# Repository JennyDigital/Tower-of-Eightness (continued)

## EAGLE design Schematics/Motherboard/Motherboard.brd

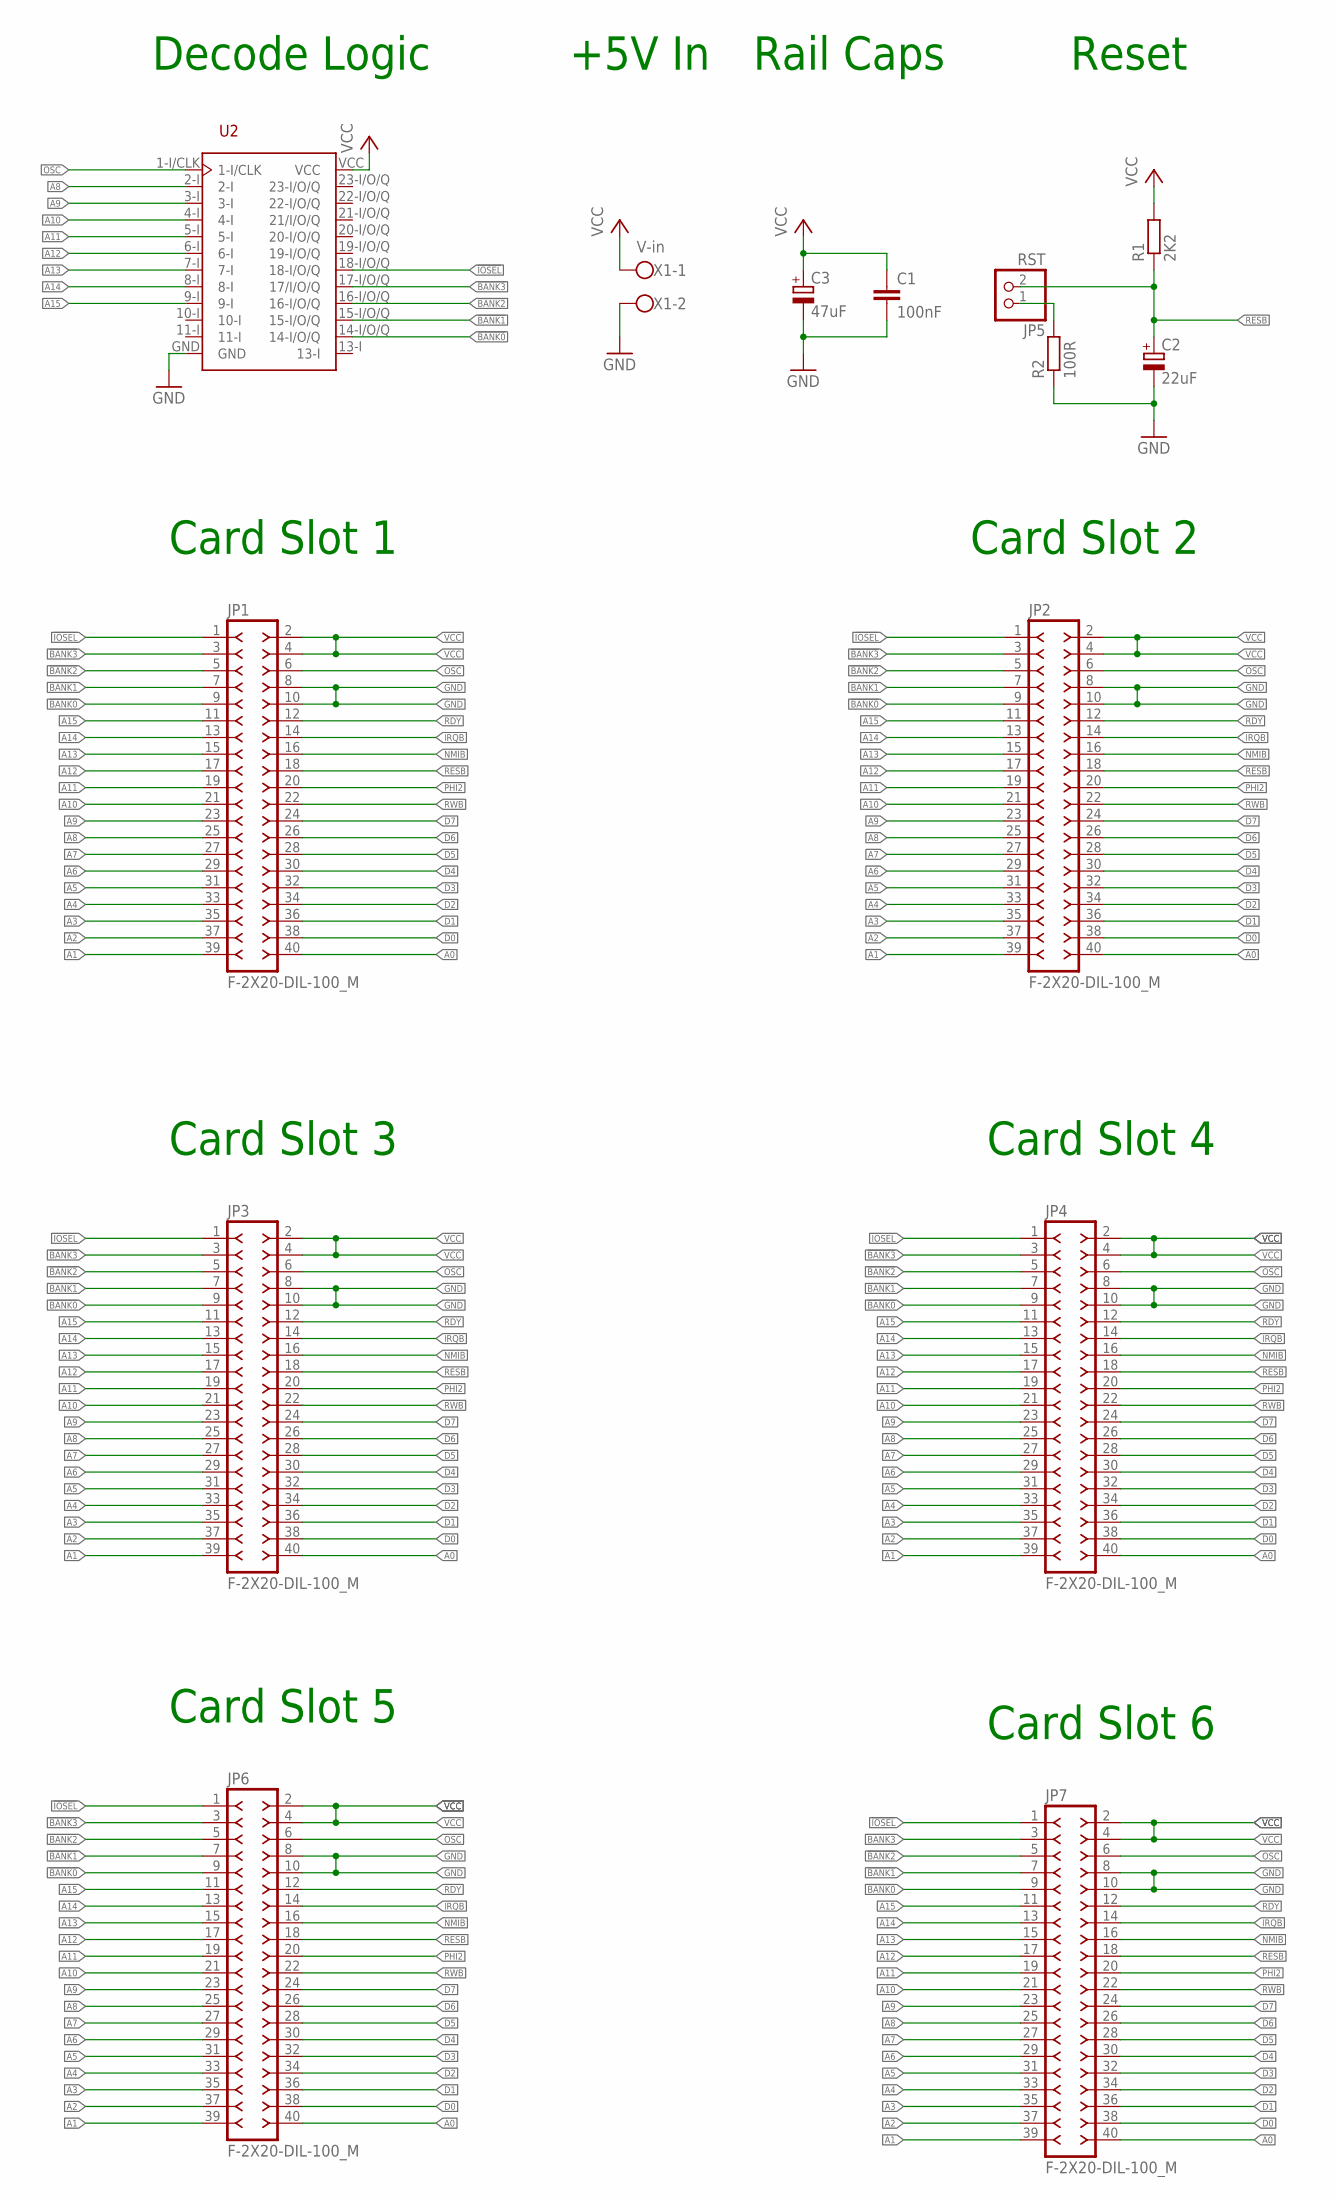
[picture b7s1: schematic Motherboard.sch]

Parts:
C1: 100nF; C050-025X075
C2: 22uF; E2-5
C3: 47uF; E2,5-7
JP1, JP2, JP3, JP4, JP6, JP7: F-2X20-DIL-100_M; DIL-100-2X20_M
JP5: RST; 1X02
R1: 2K2; 0207/10
R2: 100R; 0207/10
U2: GAL22V10D-DIP; DIP24
X1: V-in; W237-102

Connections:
!BANK0: JP1.9, JP2.9, JP3.9, JP4.9, JP6.9, JP7.9, U2.14-I/O/Q
!BANK1: JP1.7, JP2.7, JP3.7, JP4.7, JP6.7, JP7.7, U2.15-I/O/Q
!BANK2: JP1.5, JP2.5, JP3.5, JP4.5, JP6.5, JP7.5, U2.16-I/O/Q
!BANK3: JP1.3, JP2.3, JP3.3, JP4.3, JP6.3, JP7.3, U2.17-I/O/Q (17/I/O/Q)
!IOSEL: JP1.1, JP2.1, JP3.1, JP4.1, JP6.1, JP7.1, U2.18-I/O/Q
A0: JP1.40, JP2.40, JP3.40, JP4.40, JP6.40, JP7.40
A1: JP1.39, JP2.39, JP3.39, JP4.39, JP6.39, JP7.39
A2: JP1.37, JP2.37, JP3.37, JP4.37, JP6.37, JP7.37
A3: JP1.35, JP2.35, JP3.35, JP4.35, JP6.35, JP7.35
A4: JP1.33, JP2.33, JP3.33, JP4.33, JP6.33, JP7.33
A5: JP1.31, JP2.31, JP3.31, JP4.31, JP6.31, JP7.31
A6: JP1.29, JP2.29, JP3.29, JP4.29, JP6.29, JP7.29
A7: JP1.27, JP2.27, JP3.27, JP4.27, JP6.27, JP7.27
A8: JP1.25, JP2.25, JP3.25, JP4.25, JP6.25, JP7.25, U2.2-I
A9: JP1.23, JP2.23, JP3.23, JP4.23, JP6.23, JP7.23, U2.3-I
A10: JP1.21, JP2.21, JP3.21, JP4.21, JP6.21, JP7.21, U2.4-I
A11: JP1.19, JP2.19, JP3.19, JP4.19, JP6.19, JP7.19, U2.5-I
A12: JP1.17, JP2.17, JP3.17, JP4.17, JP6.17, JP7.17, U2.6-I
A13: JP1.15, JP2.15, JP3.15, JP4.15, JP6.15, JP7.15, U2.7-I
A14: JP1.13, JP2.13, JP3.13, JP4.13, JP6.13, JP7.13, U2.8-I
A15: JP1.11, JP2.11, JP3.11, JP4.11, JP6.11, JP7.11, U2.9-I
D0: JP1.38, JP2.38, JP3.38, JP4.38, JP6.38, JP7.38
D1: JP1.36, JP2.36, JP3.36, JP4.36, JP6.36, JP7.36
D2: JP1.34, JP2.34, JP3.34, JP4.34, JP6.34, JP7.34
D3: JP1.32, JP2.32, JP3.32, JP4.32, JP6.32, JP7.32
D4: JP1.30, JP2.30, JP3.30, JP4.30, JP6.30, JP7.30
D5: JP1.28, JP2.28, JP3.28, JP4.28, JP6.28, JP7.28
D6: JP1.26, JP2.26, JP3.26, JP4.26, JP6.26, JP7.26
D7: JP1.24, JP2.24, JP3.24, JP4.24, JP6.24, JP7.24
GND: C1.2, C2.-, C3.-, JP1.8, JP1.10, JP2.8, JP2.10, JP3.8, JP3.10, JP4.8, JP4.10, JP6.8, JP6.10, JP7.8, JP7.10, R2.1, U2.GND, X1.2
IRQB: JP1.14, JP2.14, JP3.14, JP4.14, JP6.14, JP7.14
unnamed: JP5.1, R2.2
NMIB: JP1.16, JP2.16, JP3.16, JP4.16, JP6.16, JP7.16
OSC: JP1.6, JP2.6, JP3.6, JP4.6, JP6.6, JP7.6, U2.1-I/CLK
PHI2: JP1.20, JP2.20, JP3.20, JP4.20, JP6.20, JP7.20
RDY: JP1.12, JP2.12, JP3.12, JP4.12, JP6.12, JP7.12
RESB: C2.+, JP1.18, JP2.18, JP3.18, JP4.18, JP5.2, JP6.18, JP7.18, R1.1
RWB: JP1.22, JP2.22, JP3.22, JP4.22, JP6.22, JP7.22
VCC: C1.1, C3.+, JP1.2, JP1.4, JP2.2, JP2.4, JP3.2, JP3.4, JP4.2, JP4.4, JP6.2, JP6.4, JP7.2, JP7.4, R1.2, U2.VCC, X1.1

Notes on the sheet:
Decode Logic
Card Slot 1
Card Slot 2
Card Slot 3
Card Slot 4
Reset
+5V In
Rail Caps
Card Slot 5
Card Slot 6

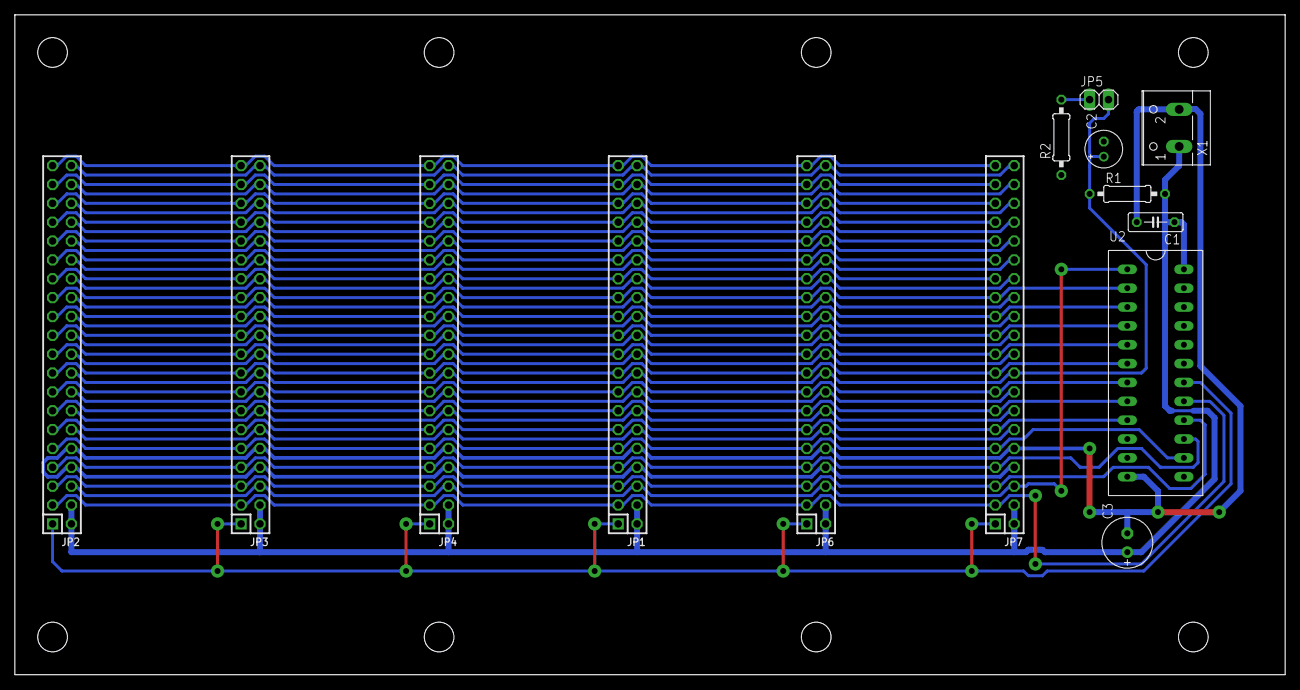
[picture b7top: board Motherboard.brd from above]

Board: 2 copper layers, 171.1 x 88.9 mm, 14 parts (0 on the bottom side), 39 nets.

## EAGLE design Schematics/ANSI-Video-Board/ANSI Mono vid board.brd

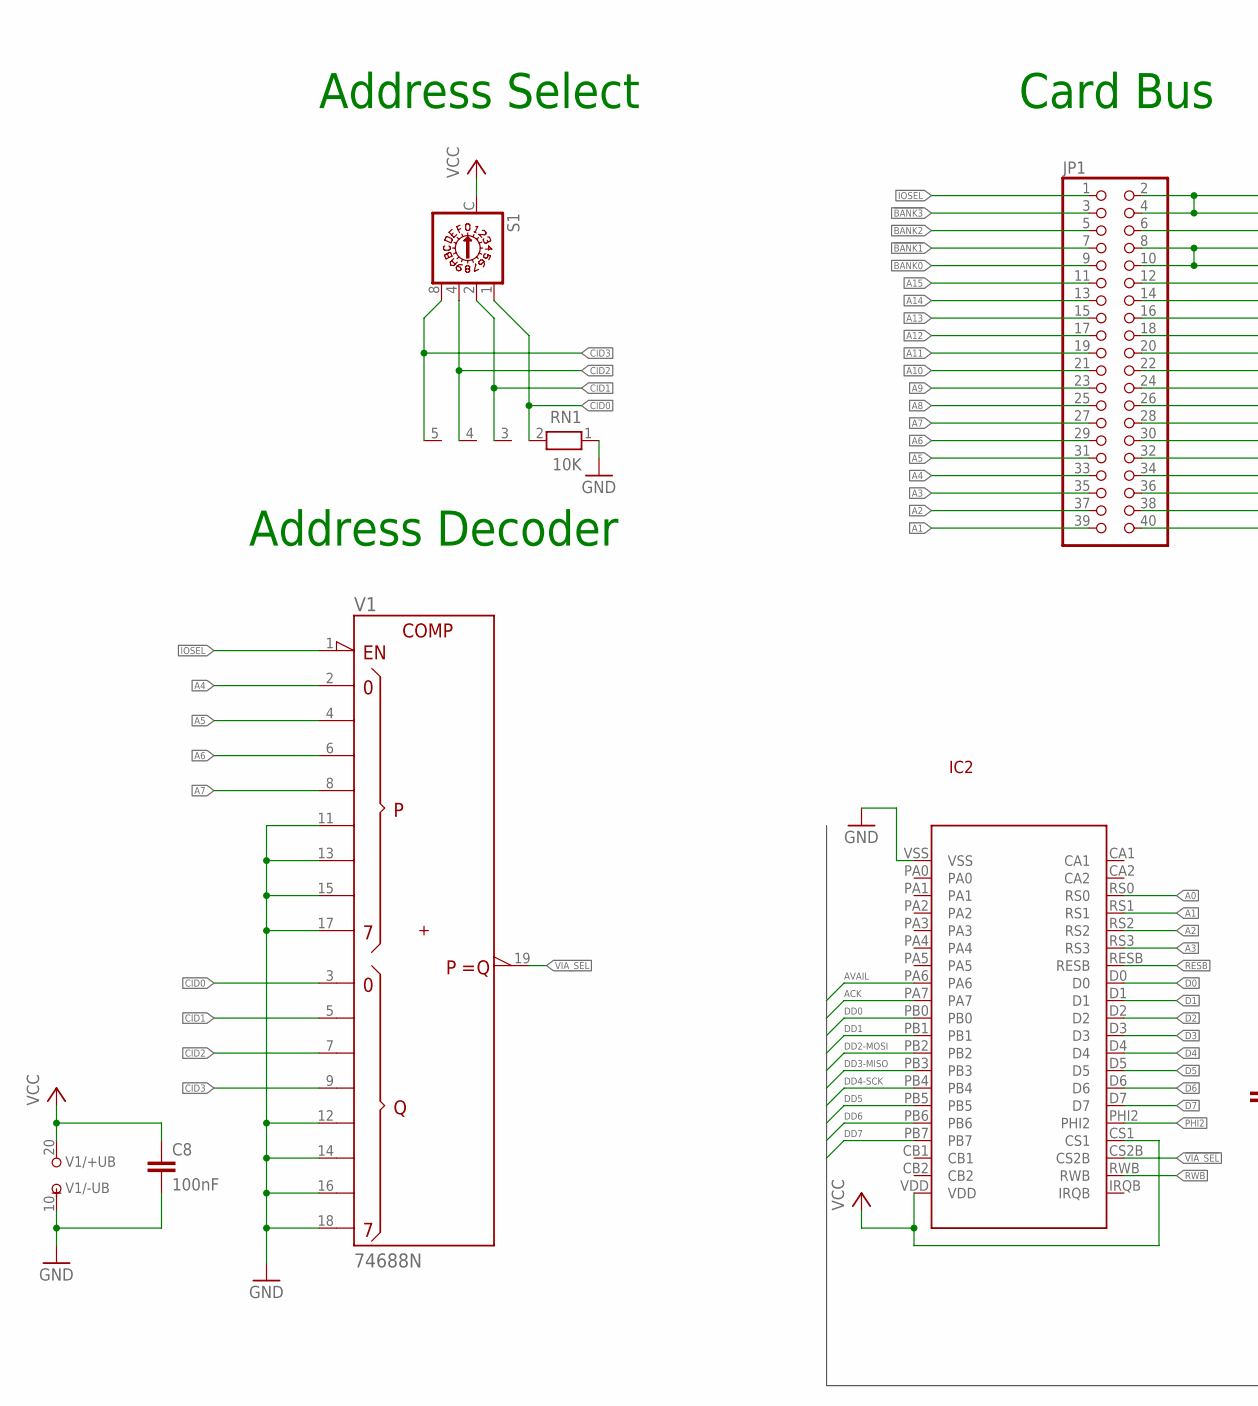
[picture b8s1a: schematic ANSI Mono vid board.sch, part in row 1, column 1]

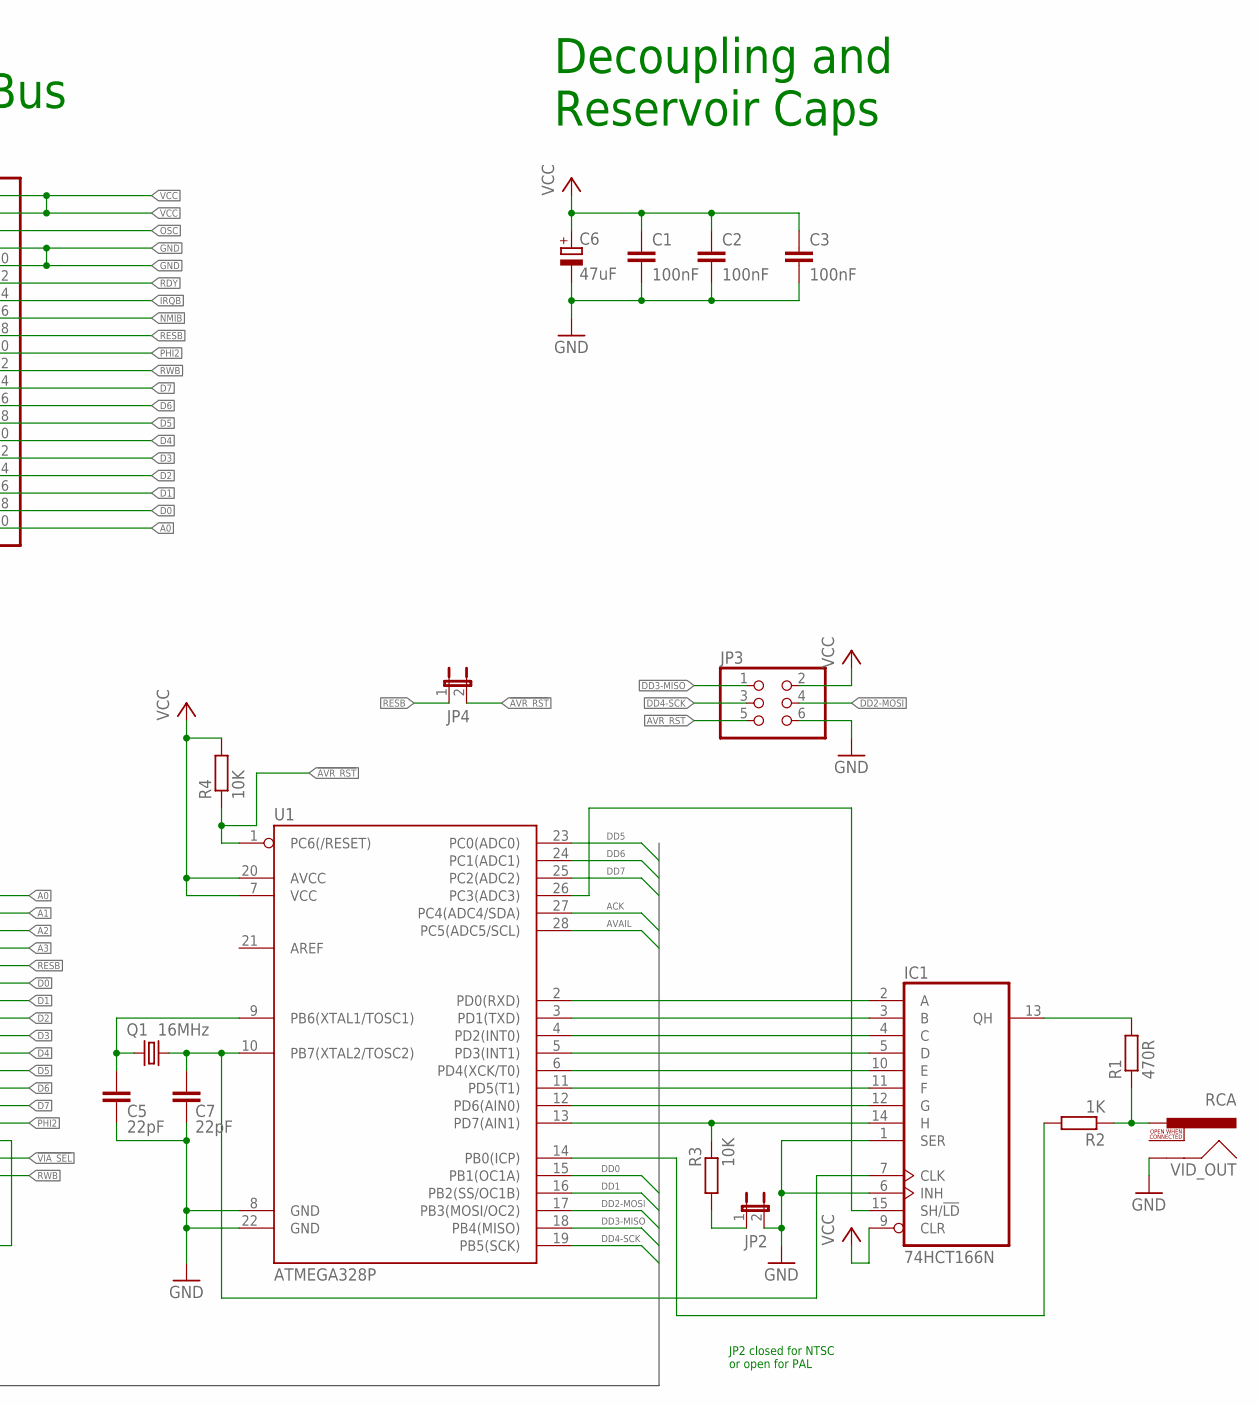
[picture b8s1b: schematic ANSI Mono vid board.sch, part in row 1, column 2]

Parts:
C1, C2, C8: 100nF; C050-025X075
C3: 100nF; C025-025X050
C5, C7: 22pF; C050-025X075
C6: 47uF; E2,5-7
IC1: 74HCT166N; DIL16
IC2: W65C22; W65C22-DIP
JP1: PINHD-2X20/90; 2X20/90
JP2, JP4: JP1E; JP1
JP3: PINHD-2X3; 2X03
Q1: 16MHz; HC49U-V
R1: 470R; 0207/10
R2: 1K; 0207/10
R3: 10K; 0207/2V
R4: 10K; 0207/7
RN1: 10K; RN-5
S1: DRR3016; DRR3010
U1: ATMEGA328P; DIL28-3
V1: 74688N; DIL20
VID_OUT: RCA

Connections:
!AVR_RST: JP3.5, JP4.2, R4.1, U1.1 (PC6(/RESET))
!BANK0: JP1.9
!BANK1: JP1.7
!BANK2: JP1.5
!BANK3: JP1.3
!IOSEL: JP1.1, V1.1 (!G)
!VIA_SEL: IC2.CS2B, V1.19 (!P=Q)
A0: IC2.RS0, JP1.40
A1: IC2.RS1, JP1.39
A2: IC2.RS2, JP1.37
A3: IC2.RS3, JP1.35
A4: JP1.33, V1.2 (P0)
A5: JP1.31, V1.4 (P1)
A6: JP1.29, V1.6 (P2)
A7: JP1.27, V1.8 (P3)
A8: JP1.25
A9: JP1.23
A10: JP1.21
A11: JP1.19
A12: JP1.17
A13: JP1.15
A14: JP1.13
A15: JP1.11
ACK: IC2.PA7, U1.27 (PC4(ADC4/SDA))
AVAIL: IC2.PA6, U1.28 (PC5(ADC5/SCL))
CID0: RN1.2, S1.1, V1.3 (Q0)
CID1: RN1.3, S1.2, V1.5 (Q1)
CID2: RN1.4, S1.4, V1.7 (Q2)
CID3: RN1.5, S1.8, V1.9 (Q3)
D0: IC2.D0, JP1.38
D1: IC2.D1, JP1.36
D2: IC2.D2, JP1.34
D3: IC2.D3, JP1.32
D4: IC2.D4, JP1.30
D5: IC2.D5, JP1.28
D6: IC2.D6, JP1.26
D7: IC2.D7, JP1.24
DD0: IC2.PB0, U1.15 (PB1(OC1A))
DD1: IC2.PB1, U1.16 (PB2(SS/OC1B))
DD2-MOSI: IC2.PB2, JP3.4, U1.17 (PB3(MOSI/OC2))
DD3-MISO: IC2.PB3, JP3.1, U1.18 (PB4(MISO))
DD4-SCK: IC2.PB4, JP3.3, U1.19 (PB5(SCK))
DD5: IC2.PB5, U1.23 (PC0(ADC0))
DD6: IC2.PB6, U1.24 (PC1(ADC1))
DD7: IC2.PB7, U1.25 (PC2(ADC2))
GND: C1.2, C2.2, C3.2, C5.2, C6.-, C7.2, C8.2, IC1.1 (SER), IC1.6 (INH), IC1.8 (GND), IC2.VSS, JP1.8, JP1.10, JP2.2, JP3.6, RN1.1, U1.8 (GND), U1.22 (GND), V1.10 (-UB), V1.11 (P4), V1.12 (Q4), V1.13 (P5), V1.14 (Q5), V1.15 (P6), V1.16 (Q6), V1.17 (P7), V1.18 (Q7), VID_OUT.SHELL
IRQB: JP1.14
unnamed: JP2.1, R3.1
unnamed: C5.1, Q1.2, U1.9 (PB6(XTAL1/TOSC1))
unnamed: C7.1, IC1.7 (CLK), Q1.1, U1.10 (PB7(XTAL2/TOSC2))
unnamed: IC1.2 (A), U1.2 (PD0(RXD))
unnamed: IC1.3 (B), U1.3 (PD1(TXD))
unnamed: IC1.4 (C), U1.4 (PD2(INT0))
unnamed: IC1.5 (D), U1.5 (PD3(INT1))
unnamed: IC1.10 (E), U1.6 (PD4(XCK/T0))
unnamed: IC1.11 (F), U1.11 (PD5(T1))
unnamed: IC1.12 (G), U1.12 (PD6(AIN0))
unnamed: IC1.14 (H), R3.2, U1.13 (PD7(AIN1))
unnamed: IC1.13 (QH), R1.2
unnamed: R2.2, U1.14 (PB0(ICP))
unnamed: IC1.15 (SH/!LD), U1.26 (PC3(ADC3))
unnamed: R1.1, R2.1, VID_OUT.PIN
NMIB: JP1.16
OSC: JP1.6
PHI2: IC2.PHI2, JP1.20
RDY: JP1.12
RESB: IC2.RESB, JP1.18, JP4.1
RWB: IC2.RWB, JP1.22
VCC: C1.1, C2.1, C3.1, C6.+, C8.1, IC1.9 (CLR), IC1.16 (VCC), IC2.CS1, IC2.VDD, JP1.2, JP1.4, JP3.2, R4.2, S1.C, U1.7 (VCC), U1.20 (AVCC), V1.20 (+UB)

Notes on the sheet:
Card Bus
Decoupling and Reservoir Caps
JP2 closed for NTSC or open for PAL
Address Select
Address Decoder

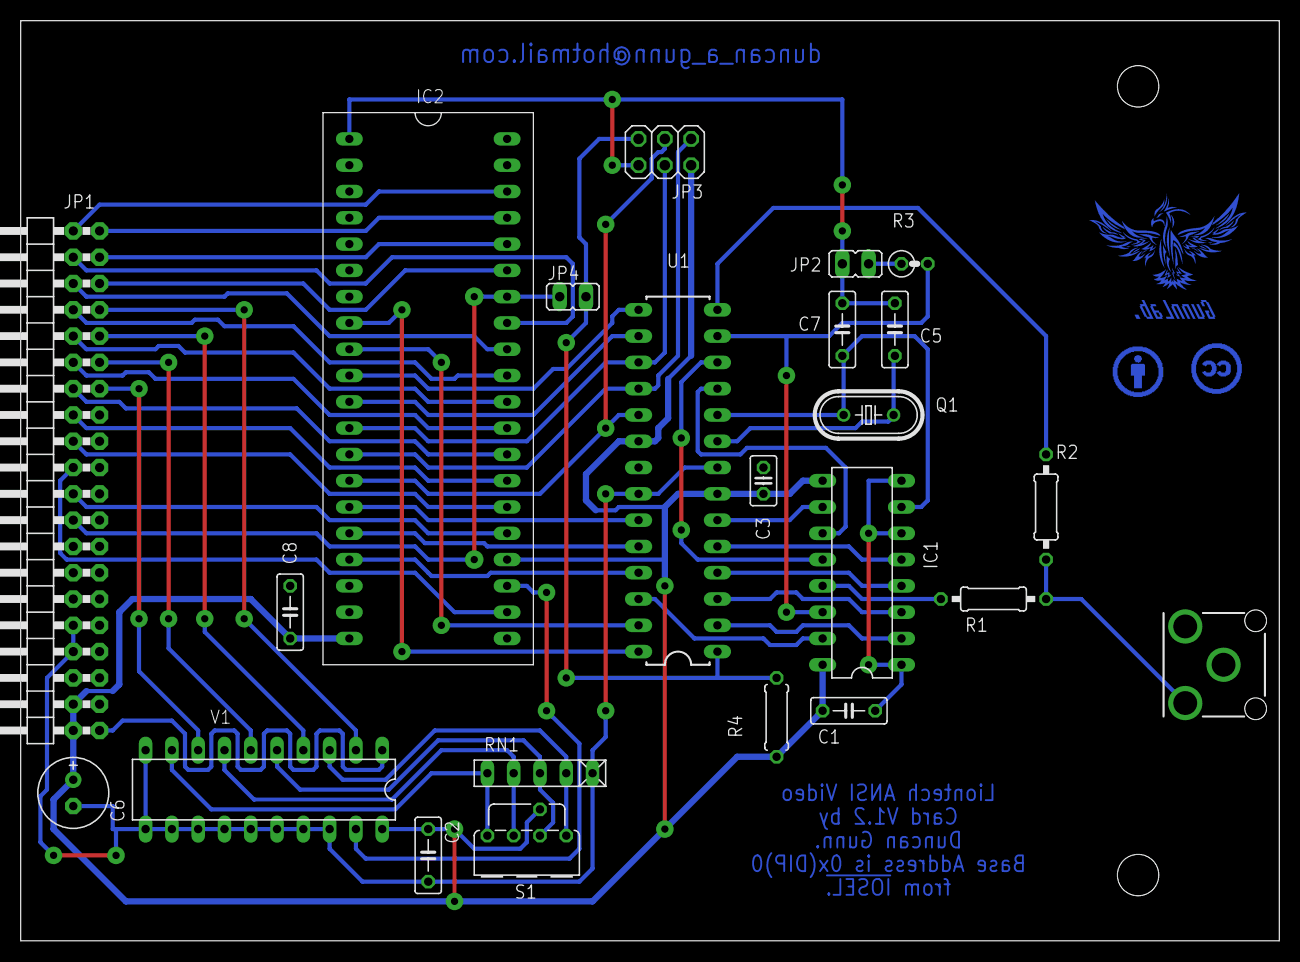
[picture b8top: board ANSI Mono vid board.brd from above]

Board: 2 copper layers, 121.6 x 88.9 mm, 26 parts (0 on the bottom side), 53 nets.

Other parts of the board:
U$1: LIONTECH
U$2: CC
U$3: BY

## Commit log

2018-06-14 First upload of project
2018-06-14 Slight change to the wording to be more correct and concise.
2018-06-15 Sign-on string updated to make the monitor start in 40 column mode
2018-06-18 Corrected text on schematic to refer to JP2 rather than JP1.
2018-06-26 Updated the processor board to add the following features:-
    Added a header for NMI and IRQ status lights.
    Reworked the circuit and added a header to allow 1, 2 and 4MHz clock speeds from the on-board oscillator.
2018-07-23 Updated the basic with Klaus2m5's patches to eradicate a couple of bugs.
    Bug 1: if two strings are equal then in direct mode they aren't!!
    Bug 2: BASIC can't find the corresponding FOR to the encountered NEXT in some instances. The same applies with DO LOOPs
    ToE_Mon.asm updated to reflect the current ROM build version.
2018-07-29 Make the ACIA swallow the first character as soon as it is initiated.
    This is a workaround until I find out why it won't read the first character from a serial keyboard but will from the PC.
2018-08-11 Got fed up with having to remove or replace all the line-feed chars in text files being sent to the ToE, so I've added a filter to the serial port.
    This is on by default but can be switched off by clearing bit 0 at $5E1 on the ToE, or by re-assembling with different defaults.
2018-08-11 Added prebuilt ROM images and a guidance note on how to use them.
2018-08-26 Small but significant error found in ToE_Mon.asm. The vector addresses listed were only counting 2 instead of 3 bytes.
    Rewritten TPBCARD TPB_tx_byte routine as the original was ugly in most ways.
    This has improved timings as a result.
2018-08-26 BUGFIX: Moved Ibuffs to 0x800 and Ram_base to make room for more features. I forgot last time. Oops!
    New feature: Now the TPB card has a routine to transmit a block of bytes.
    Update: New prebuilt ROM images to reflect recent changes.
2018-09-02 Just adding a few little listings that people can play around with.
2018-09-08 Added some underlying Tower Peripheral Bus functions to support it's use. These offer byte and block transfers. Also there's a part written function to determine which devices are calling for attenti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
2018-09-08 Put back the LF's in the listing so that it (hopefully) displays better for more people.
2018-09-09 Number of small bugs fixed and another TPB feature added. This feature allows sending a message to a device to see if it responds.
    Also, made a little more room for the TPB card's up-and-coming features.
2021-09-04 Great big update after far too long. Sorry to all those who waited patiently...
2021-09-05 Updated to have a formal Timer IRQ. Currently this is T1 on the W65C22 on the GPIO card, so if you want to use it that card must be present.
    The prebuilt ROM ToEVID.bin uses this card at 0xC040.
    A couple of minor whoopsies have been fixed as well.
2021-09-12 Added a file verify feature to the ToE. This led to the discovery of a couple of bugs in previous code, so that has been updated too.
    The manual has been adjusted accordingly, though this is still very much a
    work-in-progress. It should always be complimented with the source code.
2021-09-12 Removing of unneccesary file.
2021-09-18 Added file name support to the tape filing system.
2021-09-18 Small bug squash update. Tape file names are supposed to be upto 16 chars.
2021-09-18 Updates to the system documentation to match the code and pre-built ROM.
2021-09-19 Removal of redundant file previously used experimentally to ensure IRQ operation.
2021-09-19 The TowerTAPE filing system now checks to see what file type it is loading.
    This means that it now displays what type it is and doesn't load the wrong type.
    Also, there is a new field in the header at the start which must contain 'HEAD'.
    This is to prevent misidentification of other byte streams as headers.
    Other minor tidy-up operations have also occurred.
2021-10-03 Added keyboard support firmware including my own tweaks.
2021-10-04 I somehow miscalculated the header size, upsetting the checksum byte.
    This only manifests after a cold boot so wasn't spotted immediately.
    SORRY! All fixed now.
2021-10-04 Added new prebuilt ROM images
2021-10-31 Now supports the SAVEing, LOADing and VERIFYing of binary files
2021-10-31 Updated documentation and fixed a slight bug (Oops)
2023-03-17 Big update. It's been a while, as I've been a very poorly lady. Note, I'm in the middle of a transition having nearly died so don't expect all the documentation to contain my new name of Jennifer Gun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
2023-05-21 Upgrade to add extra commands to EhBASIC, also imroved formatting of the CAT command output.
2023-05-21 General housekeeping
2023-05-24 Remove redundant file.
2023-05-27 Enhancement to the TowerTAPE Filing System.
    BASIC files that have a filename starting with a '!' now autorun.
    Failing to load successfully is now handled with more responsibly.
    There is a new system variable for controlling the TowerTAPE FS,
    though currently there's only one meaninful bit to play with.
    Updated PDF document.
    ...Finally, this is an ongoing work of hobby nature and as such odd
2023-05-27 Preparing to use the repo in a more respectable way.
    I, sinner Jenny, vow to start doing things properly, and maybe
    slim down a bit. x
2023-05-27 Updated provision for ignoring scripts
2023-05-27 Adding repo updating automation support. This will bring changes to it faster.
2023-05-29 Make TowerBASIC smaller by removing the broken IRQ and NMI BASIC support.
    This is for two reasons:-
    1. There is a different IRQ handling system already implemented by me and being worked on
    2. The ROM space is precious for other ideas.
2023-05-29 Remove unwanted IOMAP.odt. The IO ranges are documented in the Tower Of Eightness pdf manual now.
2023-05-29 Tweaked to remove dead code for NMI and IRQ features from the source and also to remove the '?' from the INPUT prompt when prompt text is used instead.
2023-05-29 Removed previously used but no longer required file
2023-05-29 Added a new command: SPI_INIT mode,MOSI,MISO,SCK,SS,SS_ActiveLvl Added a new function: byte_in = SPI_XFER(byte_out)
    Fixed a serious bug with the SPI engine where it would receive $FF no
    matter what.
2023-06-01 Found and fixed a bug in BASICs SWAP command.
    For some reason it would only swap invalid arguments.
2023-06-03 Implemented some changes to the tape filing system to support execution of loaded binary files with a flag to switch this off if necessary.
    Implemented some changes to TowerBASIC
    1) Added some exta code and patched a SADD, VARPTR and DEEK to return
    unsigned integers
    2) Minor bugfixes.
2023-06-03 Some small changes to the address decoder WinCUPL file to make reading it easier and also to make changing the way memory works easier too.
    Other than that it's the same as far as I can tell.
2023-06-05 Added support for ^C breaking out of TAPE routines.
2023-06-05 Various small changes including performing a new when breaking out of a BASIC load.
    Documentation also updated to reflect the changes.
2023-06-07 Various tweaks to the TowerTAPE filing system etc.
    CLS can now accept an attribute as a parameter which is remembered until you change it.
2023-06-08 Added memory bounds checks to most of the modules. Tidied up a bit, updated some comments etc. Nothing big... Except added RAM based vecors for direct control of IRQ and NMI vectors.
2023-06-08 Added some improvements to the TowerTAPE FS Sundry small tweaks
2023-06-10 Small changes, nothing to write home about.
    Expeimental bits for plotting of bit blocks 'BLOBSs'
    Slight improvement to the ANSI_write Function.
2023-06-10 Removed the dodgy old TPB code, and improved slightly the Centronics code. Some slight tweaks elsewhere.
2023-06-10 A little bit of a tidy up.
2023-06-11 Microscopic tweak t code rescued from an old dropbox
2023-06-18 Found a bug in the SOUND command which affected noise. Fixed now.
2023-06-18 Ensure source version is for ANSI.
2023-06-18 Stripped out BlobPlot from the OS and committed it to it's own loadable binary.
2023-06-24 Added Selected Improvements including limit protection for the PLOT routine. Added a tool to crudely send hex files to the ToE.
2023-07-23 Small updates before I reinstall my computer, wouldn't wanna loose 'em.
2025-12-22 It's been a while, let's kick things off with my current ROM
2025-12-24 Bugfix release
2025-12-25 FIX: Adjuted initialisation to for Wrong vector value intitialised for IRQ at startup FIX: ACIA2 had incorrect vector address!
2025-12-25 Fixed a few bugs and stripped out the load at recorded address feature I couldn't make work.
2025-12-25 FEATURE:- Added an optional parameter to CLEAR to set the top of memory.
2026-05-10 CHECKPOINT CHARLIE!
2026-05-10 ADDED: LINE command to TowerBASIC
2026-05-10 Bug fix in SPI SS pin handling
2026-05-11 BUGFIX: Incorrect table meant the wrong keyword was being printed
2026-05-11 FIX: Decrement in F_TAPE_BlockOut happens in the correct place now.
2026-05-11 FIX: Improved timing tolerances on tape routines.
2026-05-12 FIX: Somewhere I managed to break LINE! It's back now though. Sorry!
2026-05-12 FEATURE: LOAD and VERIFY for the binary case can now use the saved address rather than always specifying the load address by substituting '#' in it's place.
2026-05-12 FEATURE: Added bit pattern plotting capability.
2026-05-12 FIX: Somehow, I had plot and unplot reversed after adding bit pattern plotting
2026-05-12 FIX: LINE now properly respects the bit pattern when in mode 2.
2026-05-12 REFACTOR: Made the printing in TAPE_IO.asm smaller to save EEPROM space.
2026-05-12 REFACTOR: More space savings applied this time to XTRA_BASIC.asm
2026-05-13 FIX: Improved behaviour of the AY system with a bugfix. Also saved 5 bytes.
2026-05-13 FIX: Bug squash in CenTPB.asm. 1) Strobe Ack wait fixed 2) Comment typo fixed.
    REFACTOR: Minor memory saving of 19 bytes. Not a lot, but this is an 8-bit
    system with limited resources after all.
2026-05-13 Updated Centronics code
2026-05-13 FIX: Improved filtering for ACIA inputs (mainly for the keyboard.)
2026-05-13 FIX: Keyboard interface now shows the correct caps lock state on starting FIX: Keybaord interface now givea the keyboard 500mS to wake up before starting FIX: Race condition in keyboard code fixed. F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
2026-05-13 FEATURE: PRINT can now accept #n where n is the value that sets which output streams to send the output to.
2026-05-13 Add LIST #n output selector support
2026-05-13 FEATURE: Added #n stream support to LIST.
2026-05-14 FEATURE: Added helper scripts FEATURE: Added slowcopy utility to limit the transfer rate to the ToE when sending files over the serial port as keyboard characters.
